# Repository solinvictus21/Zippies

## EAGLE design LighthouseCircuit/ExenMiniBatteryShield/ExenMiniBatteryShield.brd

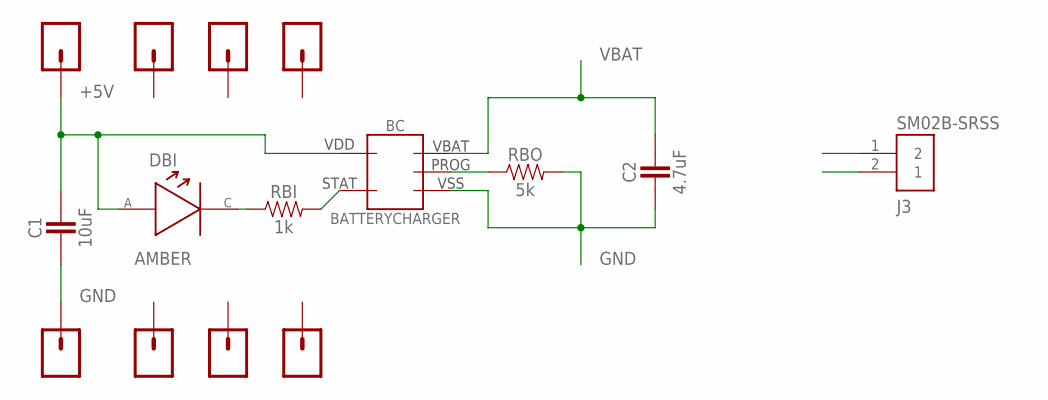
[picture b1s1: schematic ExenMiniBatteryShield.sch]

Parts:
+3.3, +5: CONN_01PTH_NO_SILK_YES_STOP; 1X01_NO_SILK
A1, A2: CONN_01PTH_NO_SILK_YES_STOP; 1X01_NO_SILK
BC: BATTERYCHARGER; SOT-753
C1: 10uF; PASSIVE-0603
C2: 4.7uF; PASSIVE-0603
DBI: AMBER; PASSIVE-0603
GND: CONN_01PTH_NO_SILK_YES_STOP; 1X01_NO_SILK
J3: SM02B-SRSS; JST_SH_2X1
RBI: 1k; PASSIVE-0603
RBO: 5k; PASSIVE-0603
RST: CONN_01PTH_NO_SILK_YES_STOP; 1X01_NO_SILK
SCL: CONN_01PTH_NO_SILK_YES_STOP; 1X01_NO_SILK
SDA: CONN_01PTH_NO_SILK_YES_STOP; 1X01_NO_SILK

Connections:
+5V: +5.1, BC.VDD, C1.2, DBI.1 (ANODE)
GND: BC.VSS, C1.1, C2.1, GND.1, J3.1 (2), RBO.2
unnamed: DBI.2 (CATHODE), RBI.1
unnamed: BC.STAT, RBI.2
unnamed: BC.PROG, RBO.1
VBAT: BC.VBAT, C2.2, J3.2 (1)

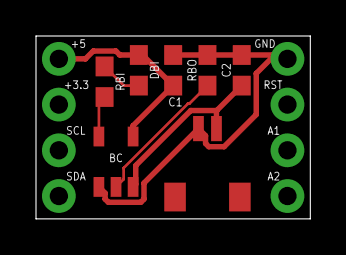
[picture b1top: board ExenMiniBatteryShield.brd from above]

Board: 2 copper layers, 15.2 x 10.2 mm, 15 parts (0 on the bottom side), 6 nets.

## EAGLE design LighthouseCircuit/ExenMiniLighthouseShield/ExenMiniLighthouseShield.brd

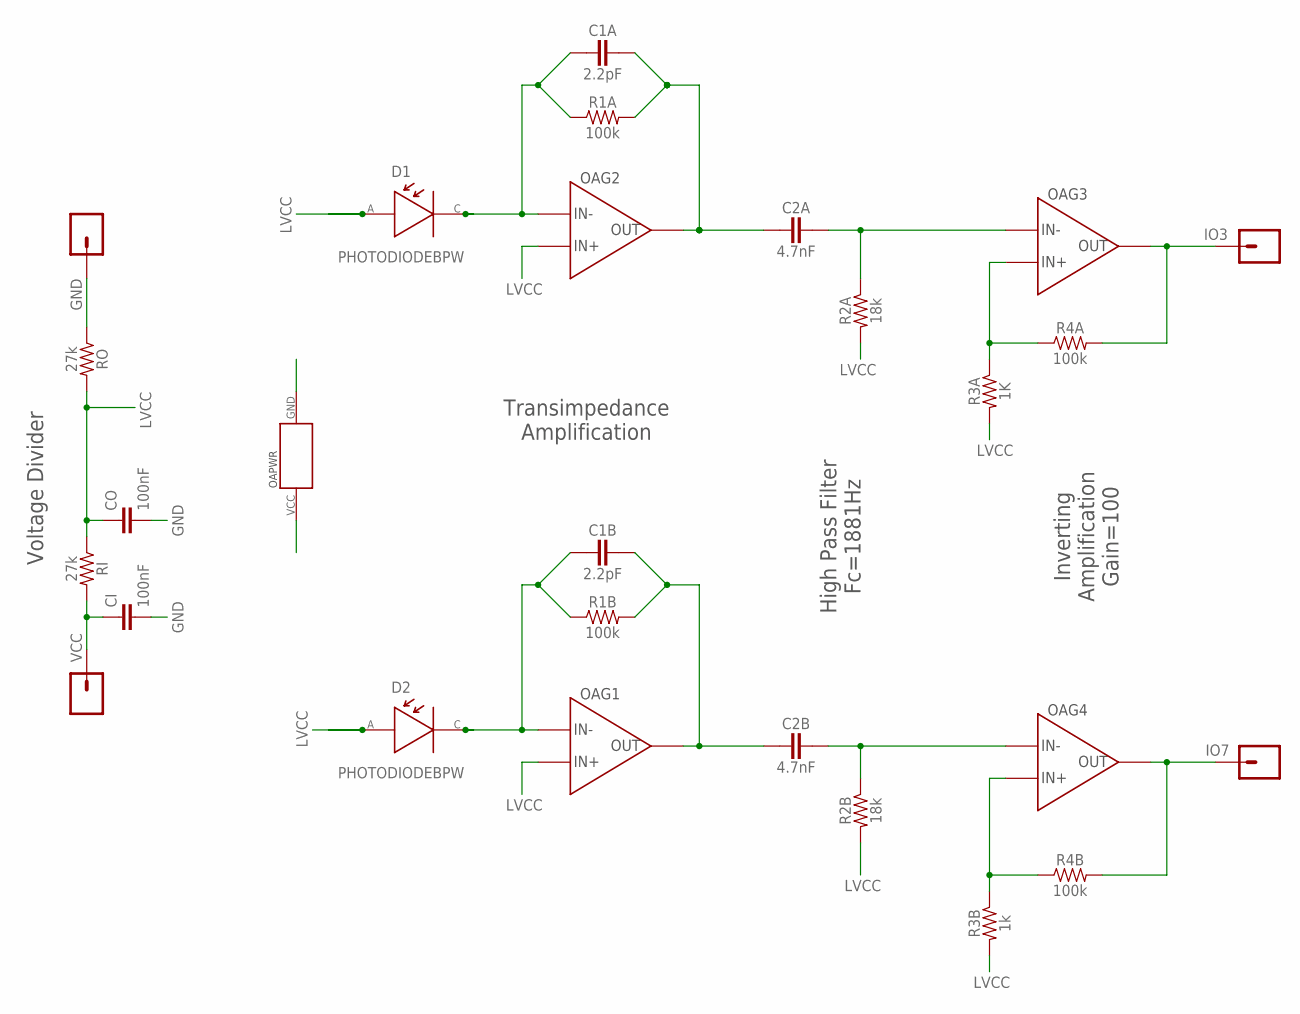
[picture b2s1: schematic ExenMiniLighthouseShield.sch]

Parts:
C1A, C1B: 2.2pF; PASSIVE-0603
C2A, C2B: 4.7nF; PASSIVE-0603
CI: 100nF; 0603
CO: 100nF; 0603
D1, D2: PHOTODIODEBPW; BPW34_BP104_SMD
GND: SINGLE-THROUGH-HOLE
IO3, IO7: CONN_01PTH_NO_SILK_YES_STOP; 1X01_NO_SILK
OA: TLV2464IDM; D14-M
R1A, R1B, R4A, R4B: 100k; PASSIVE-0603
R2A, R2B: 18k; PASSIVE-0603
R3A: 1K; PASSIVE-0603
R3B: 1k; PASSIVE-0603
RI: 27k; 0603
RO: 27k; 0603
VCC: CONN_01PTH_NO_SILK_YES_STOP; 1X01_NO_SILK

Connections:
D1IN: C1B.1, D2.CATHODE, OA.2 (IN-), R1B.1
D1OA2P: C2B.2, OA.13 (IN-), R2B.1
D1OAOUT1: C1B.2, C2B.1, OA.1 (OUT), R1B.2
D2IN: C1A.1, D1.CATHODE, OA.6 (IN-), R1A.1
D2OA1OUT: C1A.2, C2A.1, OA.7 (OUT), R1A.2
D2OA2N: OA.10 (IN+), R3A.1, R4A.1
D2OA2P: C2A.2, OA.9 (IN-), R2A.1
GND: CI.2, CO.2, GND.1, OA.11 (GND), RO.1
IO3: IO3.1, OA.8 (OUT), R4A.2
IO7: IO7.1, OA.14 (OUT), R4B.2
LVCC: CO.1, D1.ANODE, D2.ANODE, OA.3 (IN+), OA.5 (IN+), R2A.2, R2B.2, R3A.2, R3B.2, RI.1, RO.2
unnamed: OA.12 (IN+), R3B.1, R4B.1
VCC: CI.1, OA.4 (VCC), RI.2, VCC.1

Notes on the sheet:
Voltage Divider
High Pass Filter Fc=1881Hz
Transimpedance Amplification
Inverting Amplification Gain=100

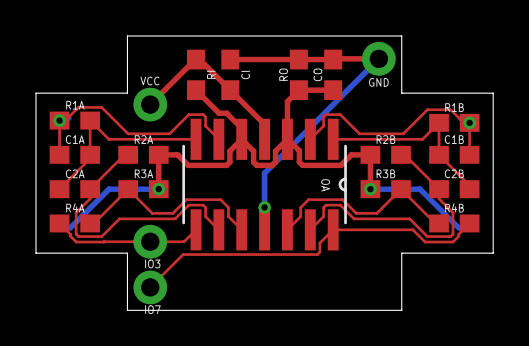
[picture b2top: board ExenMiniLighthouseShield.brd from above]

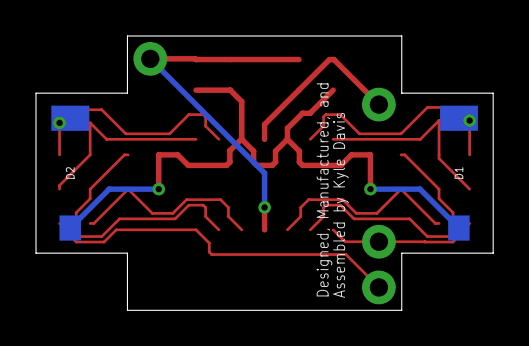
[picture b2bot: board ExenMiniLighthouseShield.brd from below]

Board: 2 copper layers, 25.4 x 15.2 mm, 23 parts (2 on the bottom side), 13 nets.

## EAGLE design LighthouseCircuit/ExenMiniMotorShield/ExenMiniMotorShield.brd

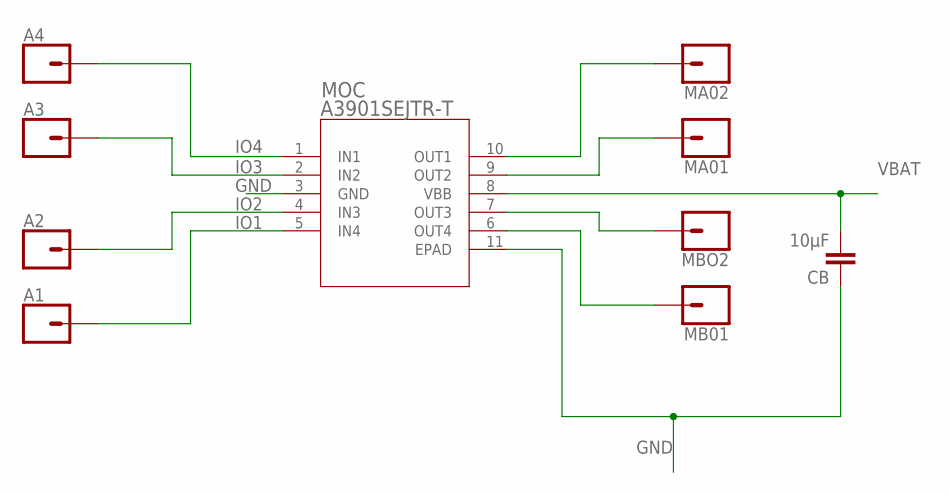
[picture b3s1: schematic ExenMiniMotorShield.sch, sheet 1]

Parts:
A1, A2, A3, A4: CONN_01PTH_NO_SILK_YES_STOP; 1X01_NO_SILK
CB: 10μF; 0603
MA01, MA02: CONN_01PTH_NO_SILK_YES_STOP; 1X01_NO_SILK
MB01: CONN_01PTH_NO_SILK_YES_STOP; 1X01_NO_SILK
MBO2: CONN_01PTH_NO_SILK_YES_STOP; 1X01_NO_SILK
MOC: A3901SEJTR-T; DFN-10_DD

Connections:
GND: CB.1, MOC.3 (GND), MOC.11 (EPAD); also elsewhere on the board
IO1: A1.1, MOC.5 (IN4)
IO2: A2.1, MOC.4 (IN3)
IO3: A3.1, MOC.2 (IN2)
IO4: A4.1, MOC.1 (IN1)
MA01: MBO2.1, MOC.7 (OUT3)
MA02: MB01.1, MOC.6 (OUT4)
MB01: MA02.1, MOC.10 (OUT1)
MB02: MA01.1, MOC.9 (OUT2)
VBAT: CB.2, MOC.8 (VBB); also elsewhere on the board

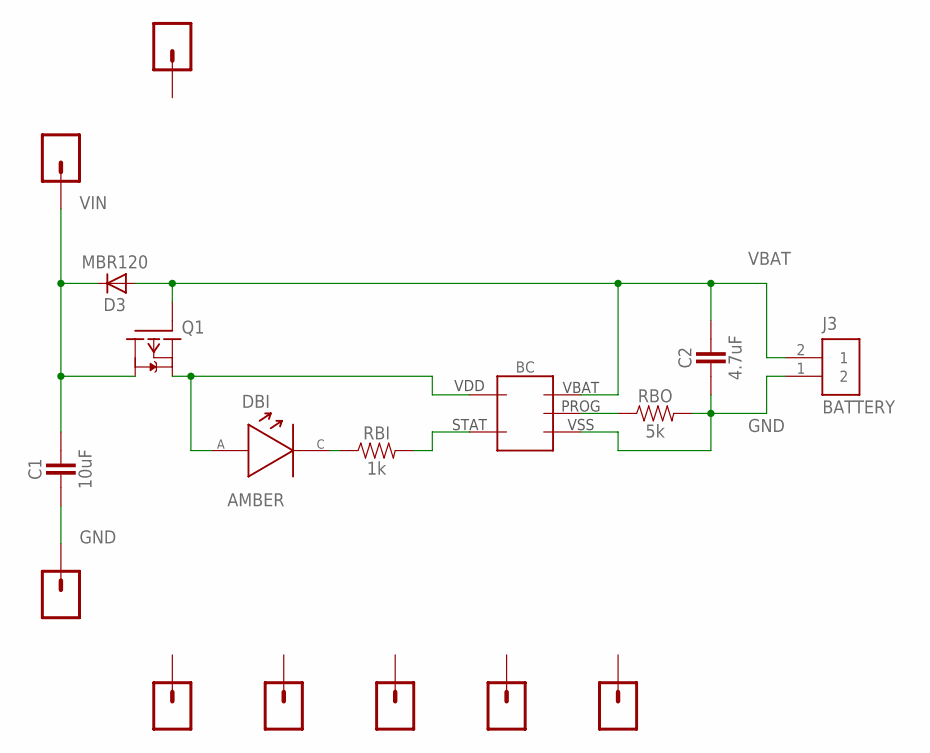
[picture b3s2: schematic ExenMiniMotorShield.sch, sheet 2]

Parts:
+3.3: CONN_01PTH_NO_SILK_YES_STOP; 1X01_NO_SILK
BC: BATTERYCHARGER; SOT-753
C1: 10uF; PASSIVE-0603
C2: 4.7uF; PASSIVE-0603
D0, D1: CONN_01PTH_NO_SILK_YES_STOP; 1X01_NO_SILK
D3: MBR120; SOD-123FL
DBI: AMBER; PASSIVE-0603
GND: CONN_01PTH_NO_SILK_YES_STOP; 1X01_NO_SILK
J3: BATTERY; JST_SH_2X1
Q1: DMP2035U; SOT23
RBI: 1k; PASSIVE-0603
RBO: 5k; PASSIVE-0603
RST: CONN_01PTH_NO_SILK_YES_STOP; 1X01_NO_SILK
SCL: CONN_01PTH_NO_SILK_YES_STOP; 1X01_NO_SILK
SDA: CONN_01PTH_NO_SILK_YES_STOP; 1X01_NO_SILK
VIN: CONN_01PTH_NO_SILK_YES_STOP; 1X01_NO_SILK

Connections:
GND: BC.VSS, C1.1, C2.1, GND.1, J3.1 (2), RBO.2; also elsewhere on the board
unnamed: DBI.2 (CATHODE), RBI.1
unnamed: BC.STAT, RBI.2
unnamed: BC.PROG, RBO.1
VBAT: BC.VBAT, C2.2, D3.A, J3.2 (1), Q1.B (G); also elsewhere on the board
VDD: BC.VDD, DBI.1 (ANODE), Q1.E (S)
VIN: C1.2, D3.C, Q1.C (D), VIN.1

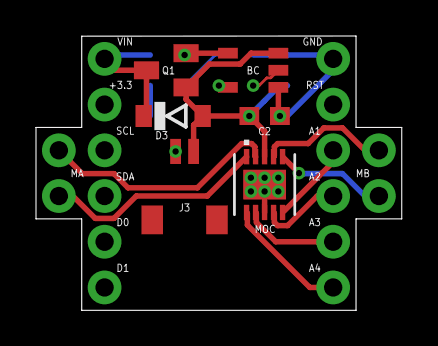
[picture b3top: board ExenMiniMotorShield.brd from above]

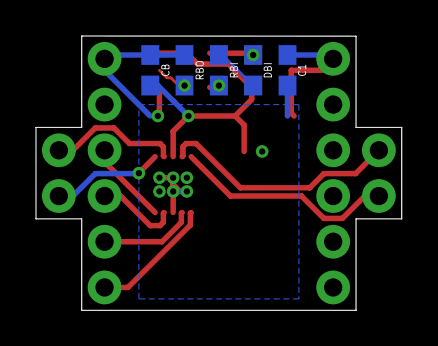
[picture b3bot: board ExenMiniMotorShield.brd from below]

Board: 2 copper layers, 20.3 x 15.2 mm, 27 parts (5 on the bottom side), 15 nets.

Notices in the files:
parts and their libraries:
SparkFun-Connectors: Licensing: Creative Commons ShareAlike 4.0 International - https://creativecommons.org/licenses/by-sa/4.0
